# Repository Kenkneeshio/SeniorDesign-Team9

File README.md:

# SeniorDesign-Team9

Currently the GitHub Repo ignores .zip and .raw to save space

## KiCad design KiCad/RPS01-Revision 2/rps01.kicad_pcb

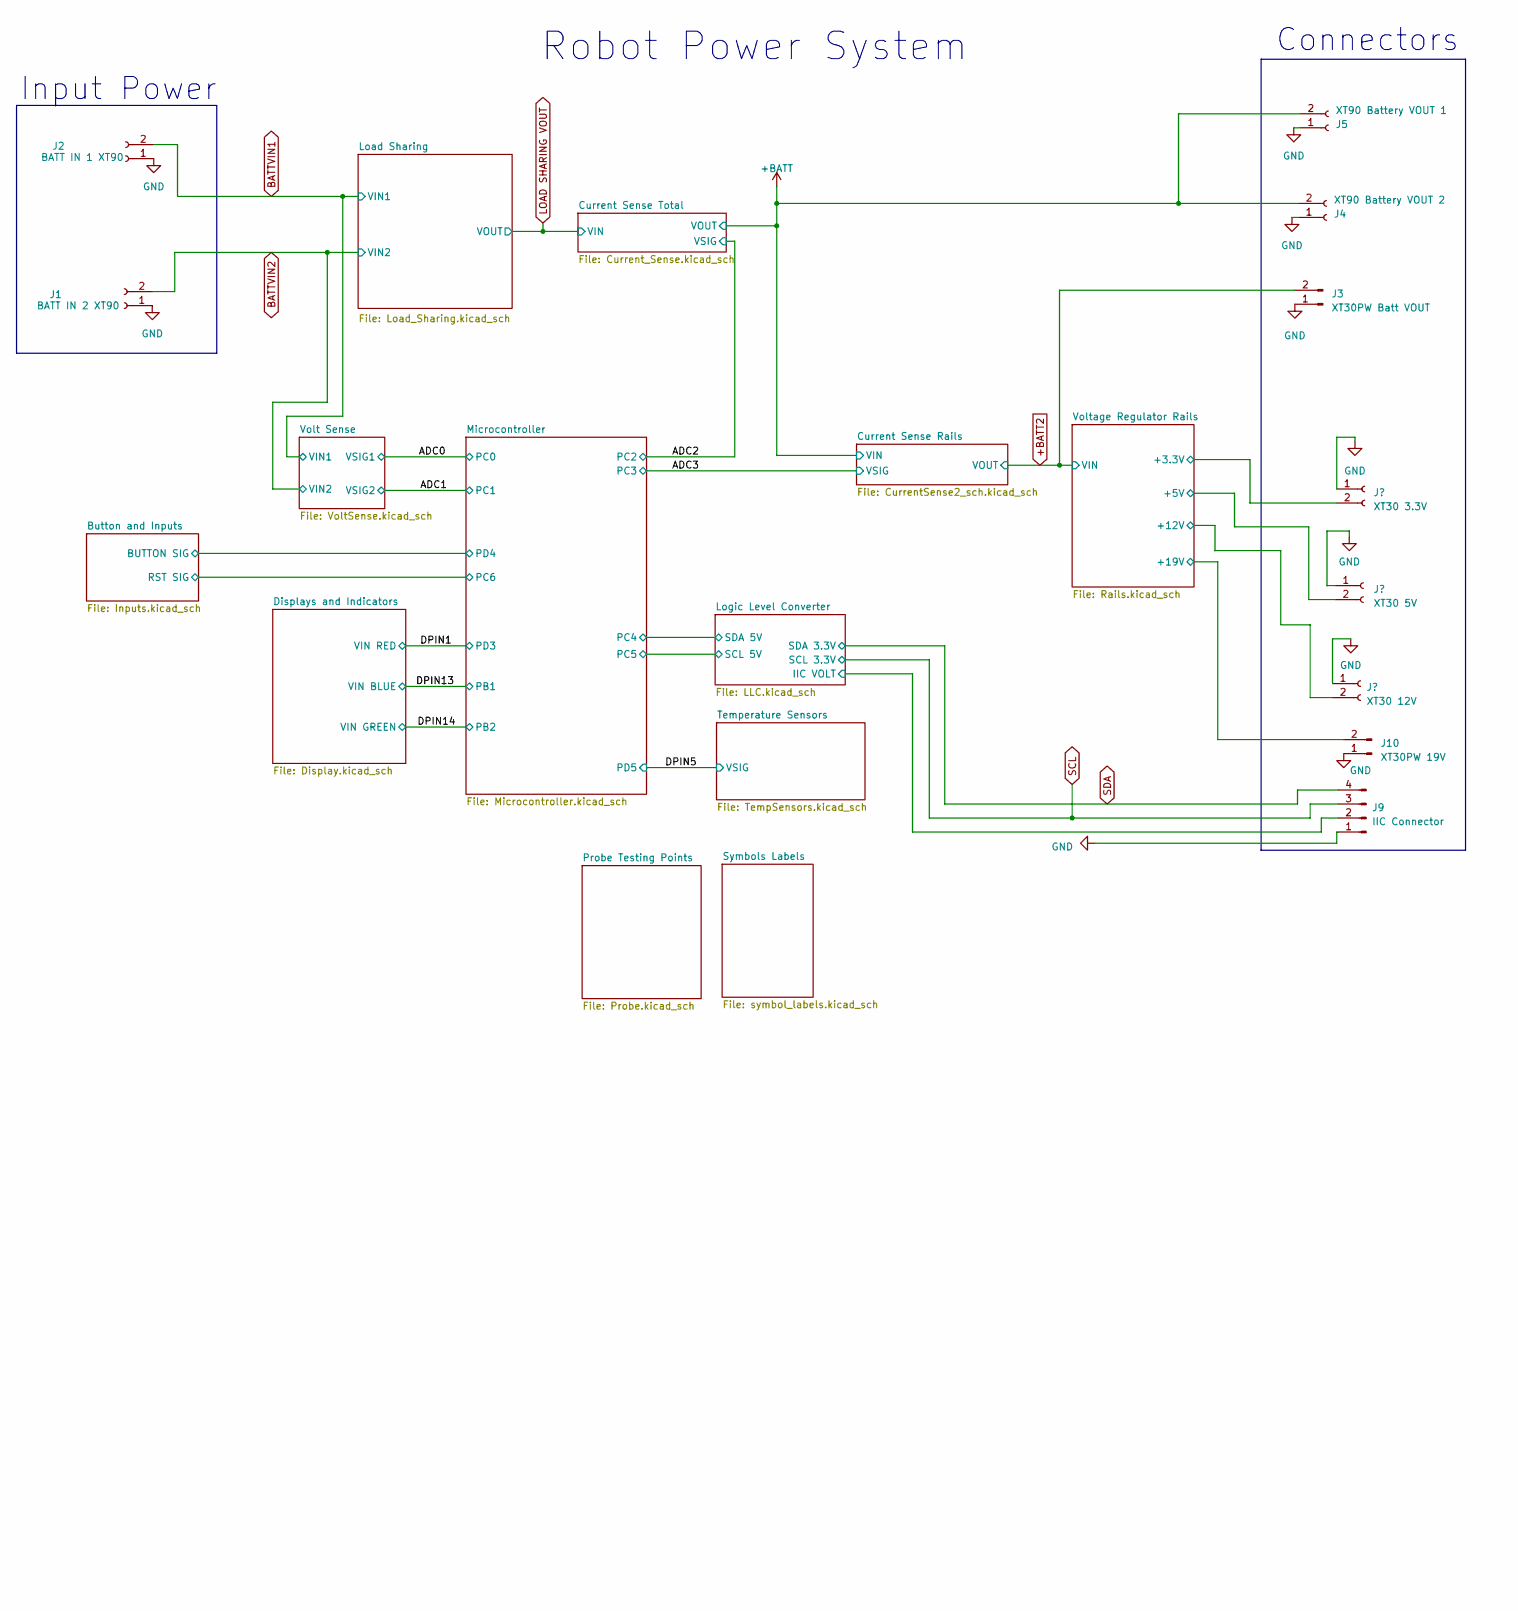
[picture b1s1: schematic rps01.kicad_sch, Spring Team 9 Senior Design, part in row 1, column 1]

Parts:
J1: BATT IN 2 XT90; AMASS_XT90-M_1x02_P11.00mm_Vertical
J2: BATT IN 1 XT90; AMASS_XT90-M_1x02_P11.00mm_Vertical
J3: XT30PW Batt VOUT; AMASS_XT30PW-F_1x02_P2.50mm_Horizontal
J4: XT90 Battery VOUT 2; AMASS_XT90-F_1x02_P11.00mm_Vertical
J5: XT90 Battery VOUT 1; AMASS_XT90-F_1x02_P11.00mm_Vertical
J6: XT30 12V; AMASS_XT30U-F_1x02_P5.0mm_Vertical
J7: XT30 5V; AMASS_XT30U-F_1x02_P5.0mm_Vertical
J8: XT30 3.3V; AMASS_XT30U-F_1x02_P5.0mm_Vertical
J9: IIC Connector; JST_PH_B4B-PH-K_1x04_P2.00mm_Vertical
J10: XT30PW 19V; AMASS_XT30PW-F_1x02_P2.50mm_Horizontal

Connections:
+3.3V: J8.2; also elsewhere on the board
+5V: J7.2; also elsewhere on the board
+12V: J6.2; also elsewhere on the board
+19V: J10.2; also elsewhere on the board
+BATT: J4.2, J5.2; also elsewhere on the board
+BATT2: J3.2; also elsewhere on the board
/Logic Level Converter/IIC VOLT: J9.2; also elsewhere on the board
SCL: J9.3; also elsewhere on the board
SDA: J9.4; also elsewhere on the board

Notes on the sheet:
Connectors
Robot Power System
Input Power

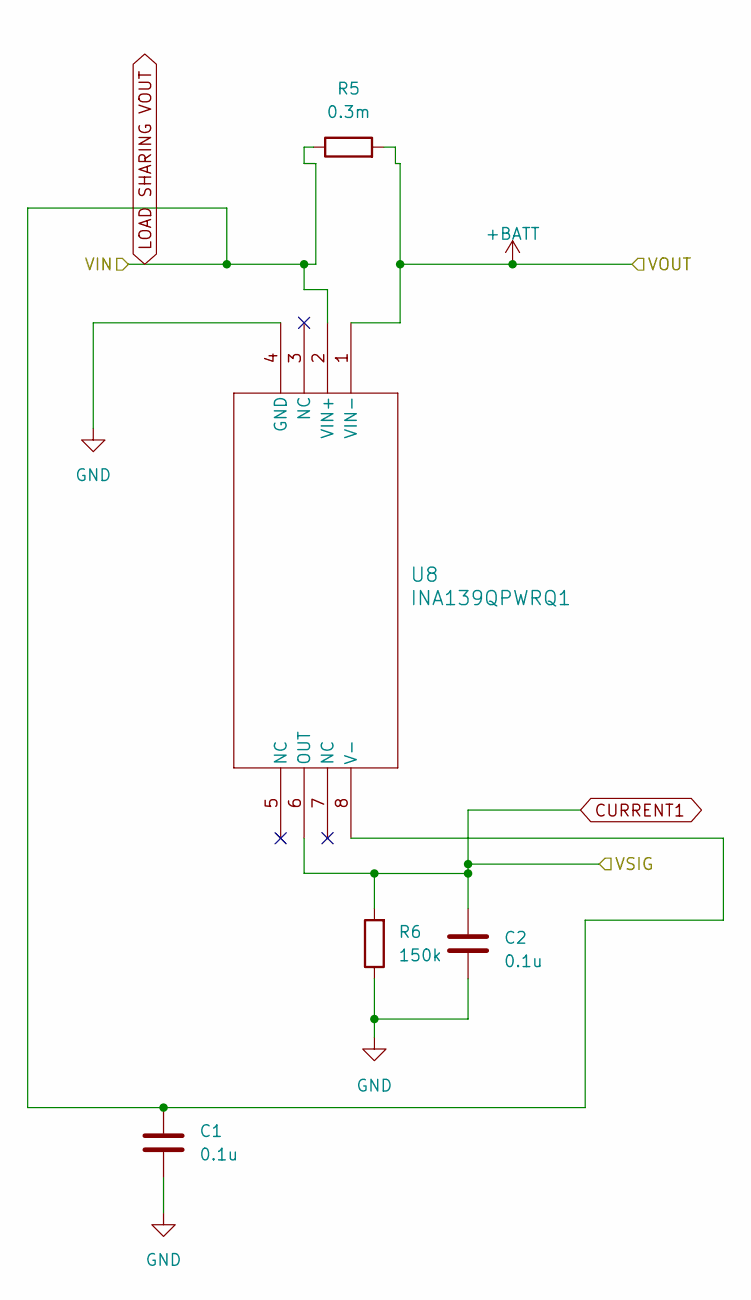
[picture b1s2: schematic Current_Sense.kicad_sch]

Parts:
C1, C2: 0.1u; C_0603_1608Metric
R5: 0.3m; CSS2H-5930R
R6: 150k; R_0603_1608Metric
U8: INA139QPWRQ1; INA139_PW8

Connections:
+BATT: R5.2, U8.1 (VIN-); also elsewhere on the board
CURRENT1: C2.1, R6.2, U8.6 (OUT); also elsewhere on the board
LOAD SHARING VOUT: C1.1, R5.1, U8.2 (VIN+), U8.8 (V-); also elsewhere on the board

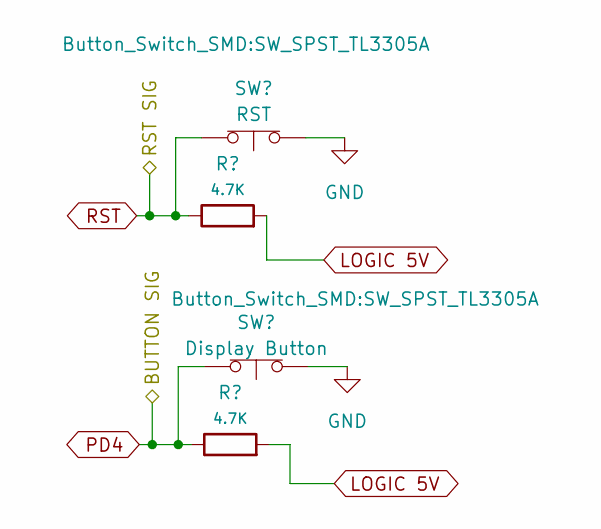
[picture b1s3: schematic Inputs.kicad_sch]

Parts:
R54, R55: 4.7K; R_0603_1608Metric
SW1: RST; SW_SPST_TL3305A
SW2: Display Button; SW_SPST_TL3305A

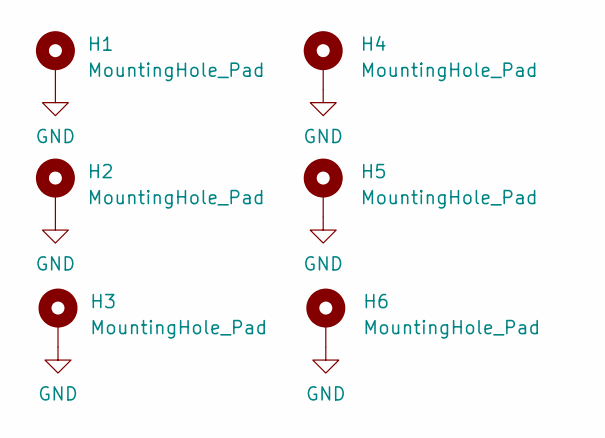
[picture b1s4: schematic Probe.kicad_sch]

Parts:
H1, H2, H3, H4, H5, H6: MountingHole_Pad; MountingHole_3.2mm_M3_Pad_Via

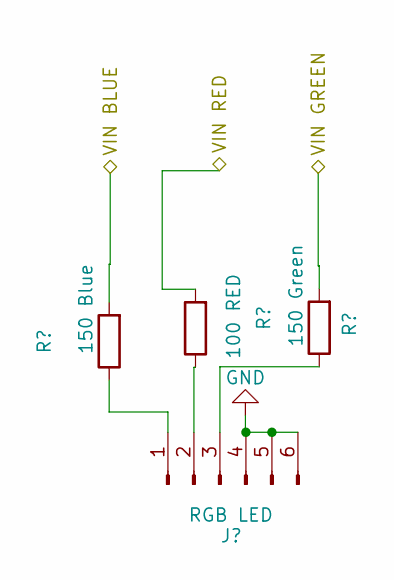
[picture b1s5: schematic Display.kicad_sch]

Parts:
J18: RGB LED; LED_RGB_5050-6
RBLUE1: 150 Blue; R_0603_1608Metric
RGREEN1: 150 Green; R_0603_1608Metric
RRED1: 100 RED; R_0603_1608Metric

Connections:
/DPIN1: RRED1.2; also elsewhere on the board
/DPIN14: RGREEN1.2; also elsewhere on the board
unnamed: J18.1, RBLUE1.1
unnamed: J18.2, RRED1.1
unnamed: J18.3, RGREEN1.1

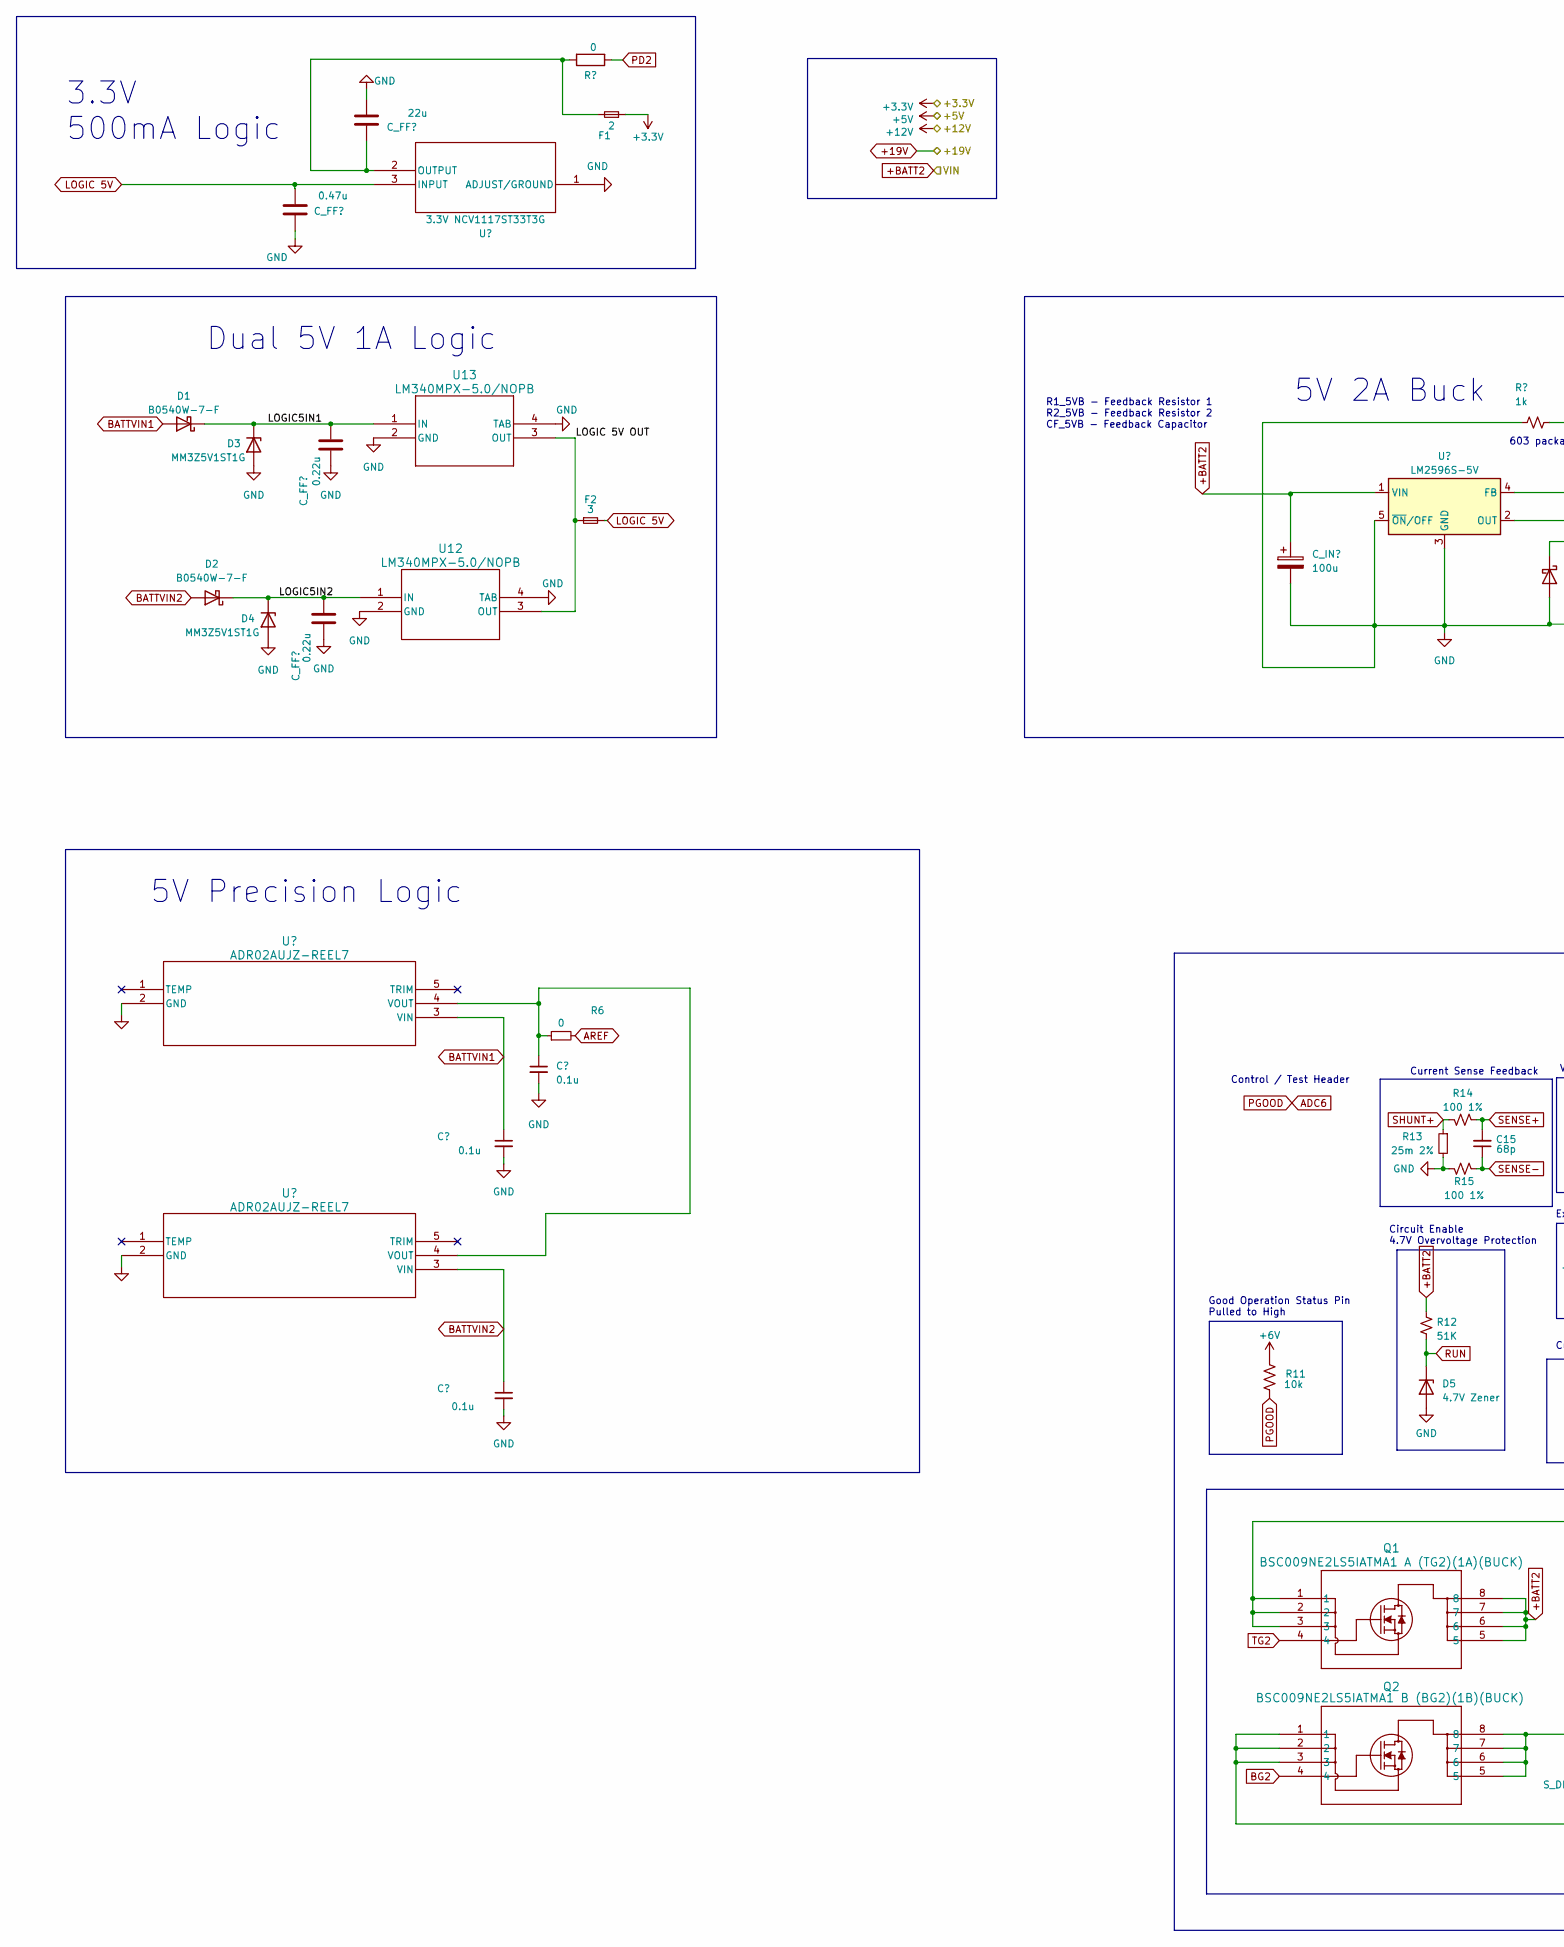
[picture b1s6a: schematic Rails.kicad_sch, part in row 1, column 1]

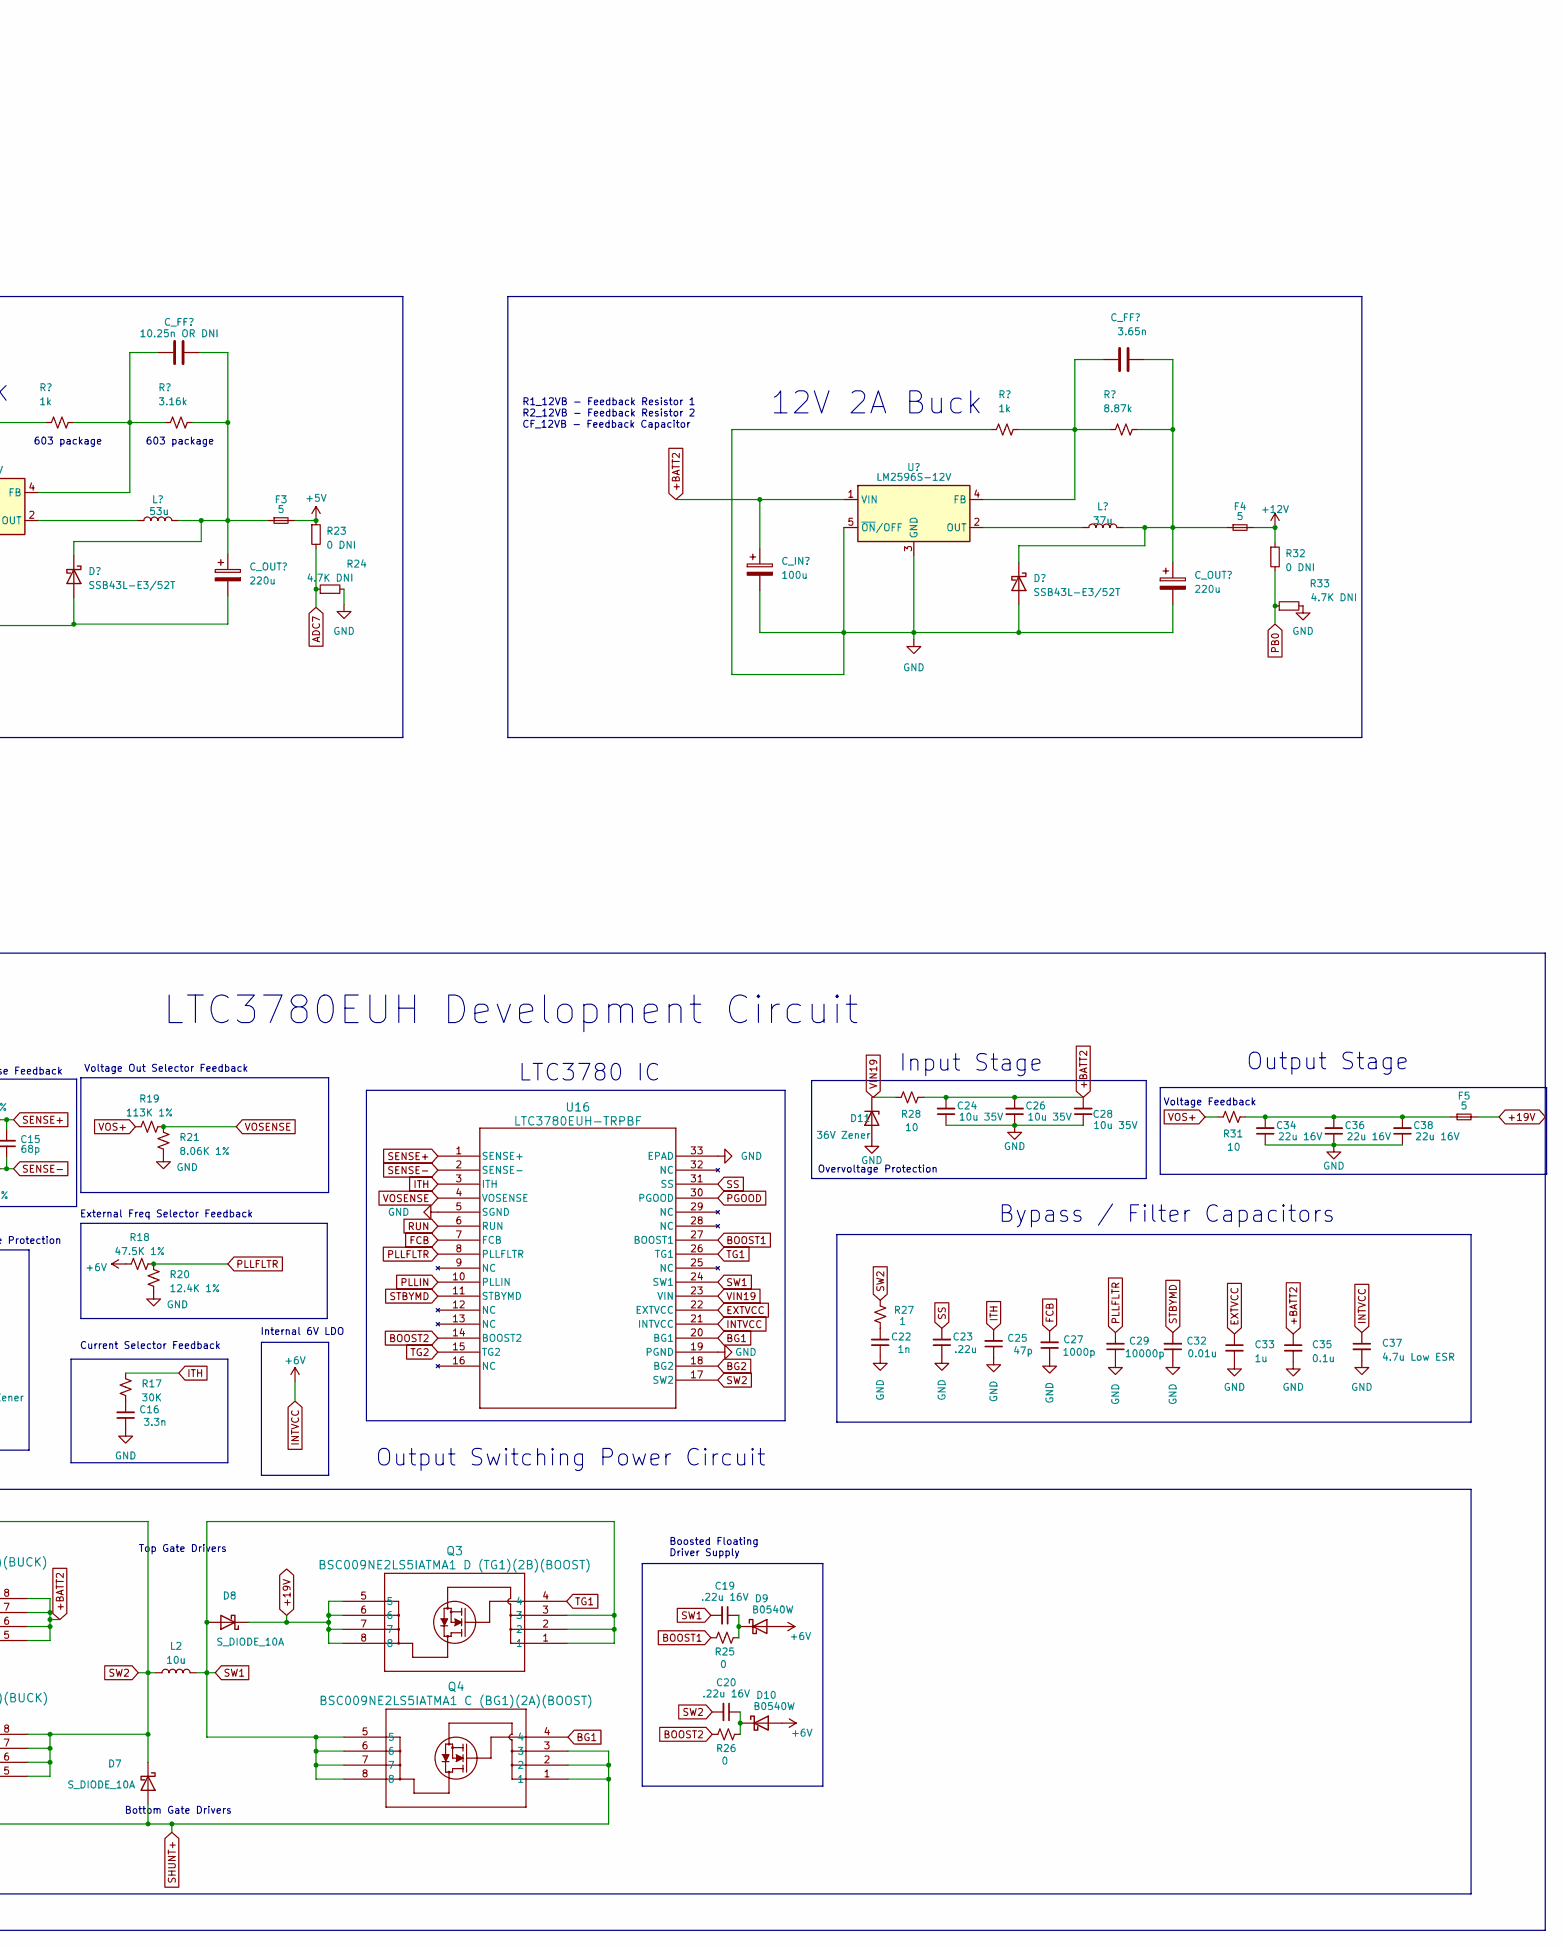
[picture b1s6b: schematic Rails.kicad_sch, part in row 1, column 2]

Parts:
C6, C7: 0.1u; C_0603_1608Metric
C8, C9: 0.22u; C_0603_1608Metric
C10: 22u; C_0603_1608Metric
C14, C21: 100u; CP_Elec_8x10
C15: 68p; C_1206_3216Metric_Pad1.33x1.80mm_HandSolder
C16: 3.3n; C_1206_3216Metric_Pad1.33x1.80mm_HandSolder
C17: 10.25n OR DNI; C_0603_1608Metric
C18, C31: 220u; CP_Elec_8x10
C19, C20: .22u 16V; C_1206_3216Metric_Pad1.33x1.80mm_HandSolder
C22: 1n; C_1206_3216Metric_Pad1.33x1.80mm_HandSolder
C23: .22u; C_1206_3216Metric_Pad1.33x1.80mm_HandSolder
C24, C26, C28: 10u 35V; C_1206_3216Metric_Pad1.33x1.80mm_HandSolder
C25: 47p; C_1206_3216Metric_Pad1.33x1.80mm_HandSolder
C27: 1000p; C_1206_3216Metric_Pad1.33x1.80mm_HandSolder
C29: 10000p; C_1206_3216Metric_Pad1.33x1.80mm_HandSolder
C30: 3.65n; C_0603_1608Metric
C32: 0.01u; C_1206_3216Metric_Pad1.33x1.80mm_HandSolder
C33: 1u; C_1206_3216Metric_Pad1.33x1.80mm_HandSolder
C34, C36, C38: 22u 16V; C_1206_3216Metric_Pad1.33x1.80mm_HandSolder
C35: 0.1u; C_1206_3216Metric_Pad1.33x1.80mm_HandSolder
C37: 4.7u Low ESR; LOWESRCAPMP7.6X4.3_3.1N_KEM
D1, D2: B0540W-7-F; D_SOD-123
D3, D4: MM3Z5V1ST1G; D_SOD-323
D5: 4.7V Zener; D_SOD-123
D6, D12: SSB43L-E3/52T; SSB43L-E352T_DIODE_DO214AA_MBRS
D7, D8: S_DIODE_10A; D_PowerDI-5
D9, D10: B0540W; CR_SMA_320-340AE_DIO
D11: 36V Zener; D_SOD-123
F1: 2; 0154Series_LTF
F2: 3; 0154Series_LTF
F3, F4, F5: 5; 0154Series_LTF
L1: 53u; PE-54039SNL_IND_HCI-68_PUL
L2: 10u; IND_410680_WRE
L3: 37u; PE-53932SNLT_IND_HCI-44_PUL
Q1: BSC009NE2LS5IATMA1 A (TG2)(1A)(BUCK); PG-TDSON-8_INF
Q2: BSC009NE2LS5IATMA1 B (BG2)(1B)(BUCK); PG-TDSON-8_INF
Q3: BSC009NE2LS5IATMA1 D (TG1)(2B)(BOOST); PG-TDSON-8_INF
Q4: BSC009NE2LS5IATMA1 C (BG1)(2A)(BOOST); PG-TDSON-8_INF
R6: 0; R_0603_1608Metric
R11: 10k; R_1206_3216Metric_Pad1.30x1.75mm_HandSolder
R12: 51K; R_1206_3216Metric_Pad1.30x1.75mm_HandSolder
R13: 25m 2%; R_2512_6332Metric_Pad1.40x3.35mm_HandSolder
R14, R15: 100 1%; R_1206_3216Metric_Pad1.30x1.75mm_HandSolder
R16, R29: 1k; R_0603_1608Metric
R17: 30K; R_1206_3216Metric_Pad1.30x1.75mm_HandSolder
R18: 47.5K 1%; R_1206_3216Metric_Pad1.30x1.75mm_HandSolder
R19: 113K 1%; R_1206_3216Metric_Pad1.30x1.75mm_HandSolder
R20: 12.4K 1%; R_1206_3216Metric_Pad1.30x1.75mm_HandSolder
R21: 8.06K 1%; R_1206_3216Metric_Pad1.30x1.75mm_HandSolder
R22: 3.16k; R_0603_1608Metric
R23, R32: 0 DNI; R_0603_1608Metric
R24, R33: 4.7K DNI; R_0603_1608Metric
R25, R26: 0; R_1206_3216Metric_Pad1.30x1.75mm_HandSolder
R27: 1; R_1206_3216Metric_Pad1.30x1.75mm_HandSolder
R28, R31: 10; R_1206_3216Metric_Pad1.30x1.75mm_HandSolder
R30: 8.87k; R_0603_1608Metric
RBLUE1: 0; R_0603_1608Metric
U9: ADR02AUJZ-REEL7; ADR02AUJZ_REEL7_UJ_5_ADI
U12, U13: LM340MPX-5.0/NOPB; SOT-223-3_TabPin2
U14: 3.3V NCV1117ST33T3G; SOT-223-3_TabPin2
U15: LM2596S-5V; TO-263-5_TabPin3
U16: LTC3780EUH-TRPBF; QFN-32_UH_LIT
U17: LM2596S-12V; TO-263-5_TabPin3

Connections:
+3.3V: F1.1; also elsewhere on the board
+5V: F3.2, R23.1; also elsewhere on the board
+12V: F4.2, R32.1; also elsewhere on the board
+19V: D8.1 (K), F5.2, Q3.5, Q3.6, Q3.7, Q3.8; also elsewhere on the board
+BATT2: C14.1, C21.1, C24.2, C26.2, C28.2, C35.1, Q1.5, Q1.6, Q1.7, Q1.8, R12.1, R28.1, U15.1 (VIN), U17.1 (VIN); also elsewhere on the board
/DPIN1: U9.1 (PD3); also elsewhere on the board
/Voltage Regulator Rails/LOGIC5IN1: C9.2, D1.1 (K), D3.1 (K), U13.1 (IN)
/Voltage Regulator Rails/LOGIC5IN2: C8.2, D2.1 (K), D4.1 (K), U12.1 (IN)
/Voltage Regulator Rails/LOGIC 5V OUT: F2.1, U12.3 (OUT), U13.3 (OUT)
ADC6: R11.2, U16.30 (PGOOD); also elsewhere on the board
ADC7: R23.2, R24.1; also elsewhere on the board
BG1: Q4.4, U16.20 (BG1)
BG2: Q2.4, U16.18 (BG2)
BOOST1: R25.1, U16.27 (BOOST1)
BOOST2: R26.1, U16.14 (BOOST2)
CURRENT1: R6.2; also elsewhere on the board
EXTVCC: C33.1, U16.22 (EXTVCC)
FCB: C27.2, U16.7 (FCB)
INTVCC: C37.1, D9.2 (A), D10.2 (A), R11.1, R18.1, U16.21 (INTVCC)
ITH: C25.2, R17.1, U16.3 (ITH)
unnamed: C16.2, R17.2
unnamed: C22.2, R27.1
unnamed: C34.2, C36.2, C38.2, F5.1, R31.1
unnamed: C17.2, C18.1, D6.1 (K), F3.1, L1.2, R22.2
unnamed: C19.1, D9.1 (K), R25.2
unnamed: C20.1, D10.1 (K), R26.2
unnamed: C30.2, C31.1, D12.1 (K), F4.1, L3.2, R30.2
unnamed 47: RBLUE1.1; also elsewhere on the board
unnamed: C17.1, R16.2, R22.1, U15.4 (FB)
unnamed: L1.1, U15.2 (OUT)
unnamed: C30.1, R29.2, R30.1, U17.4 (FB)
unnamed: L3.1, U17.2 (OUT)
PB0: R32.2, R33.1; also elsewhere on the board
PLLFLTR: C29.2, R18.2, R20.1, U16.8 (PLLFLTR)
PLLIN: U16.10 (PLLIN)
RUN: D5.1 (K), R12.2, U16.6 (RUN)
SENSE+: C15.2, R14.1, U16.1 (SENSE+)
SENSE-: C15.1, R15.1, U16.2 (SENSE-)
SHUNT+: D7.2 (A), Q2.1, Q2.2, Q2.3, Q4.1, Q4.2, Q4.3, R13.1, R14.2
SS: C23.2, U16.31 (SS)
STBYMD: C32.2, U16.11 (STBYMD)
SW1: C19.2, D8.2 (A), L2.2, Q3.1, Q3.2, Q3.3, Q4.5, Q4.6, Q4.7, Q4.8, U16.24 (SW1)
SW2: C20.2, D7.1 (K), L2.1, Q1.1, Q1.2, Q1.3, Q2.5, Q2.6, Q2.7, Q2.8, R27.2, U16.17 (SW2)
TG1: Q3.4, U16.26 (TG1)
TG2: Q1.4, U16.15 (TG2)
VIN19: D11.1 (K), R28.2, U16.23 (VIN)
VOS+: R19.1, R31.2
VOSENSE: R19.2, R21.1, U16.4 (VOSENSE)

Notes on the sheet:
Voltage Feedback
Overvoltage Protection
Top Gate Drivers
Voltage Out Selector Feedback
603 package
Good Operation Status Pin Pulled to High
R1_12VB - Feedback Resistor 1 R2_12VB - Feedback Resistor 2 CF_12VB - Feedback Capacitor
5V 2A Buck
5V Precision Logic
Current Selector Feedback
LTC3780EUH Development Circuit
External Freq Selector Feedback
Control / Test Header
LTC3780 IC
Input Stage
Dual 5V 1A Logic
Bottom Gate Drivers
Boosted Floating Driver Supply
Output Switching Power Circuit
Circuit Enable 4.7V Overvoltage Protection
R1_5VB - Feedback Resistor 1 R2_5VB - Feedback Resistor 2 CF_5VB - Feedback Capacitor
Current Sense Feedback
Output Stage
Bypass / Filter Capacitors
3.3V 500mA Logic
12V 2A Buck
Internal 6V LDO

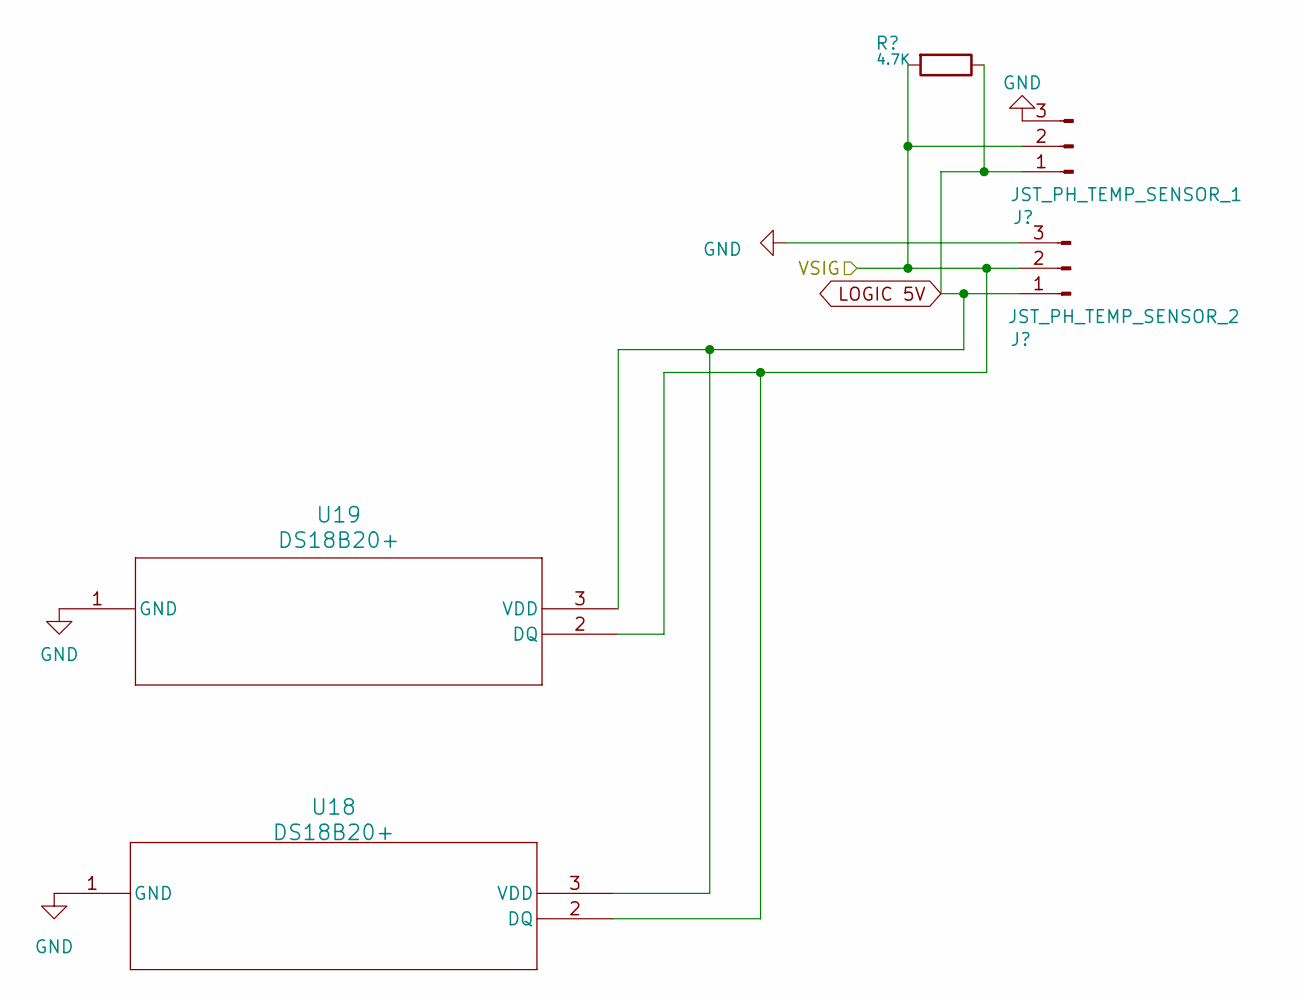
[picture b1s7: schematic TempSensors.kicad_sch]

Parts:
J16: JST_PH_TEMP_SENSOR_2; JST_PH_B3B-PH-K_1x03_P2.00mm_Vertical
J17: JST_PH_TEMP_SENSOR_1; JST_PH_B3B-PH-K_1x03_P2.00mm_Vertical
R44: 4.7K; R_0603_1608Metric
U18, U19: DS18B20+; TO-92L_Inline

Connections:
/DPIN5: J16.2, J17.2, R44.2, U18.2 (DQ), U19.2 (DQ); also elsewhere on the board

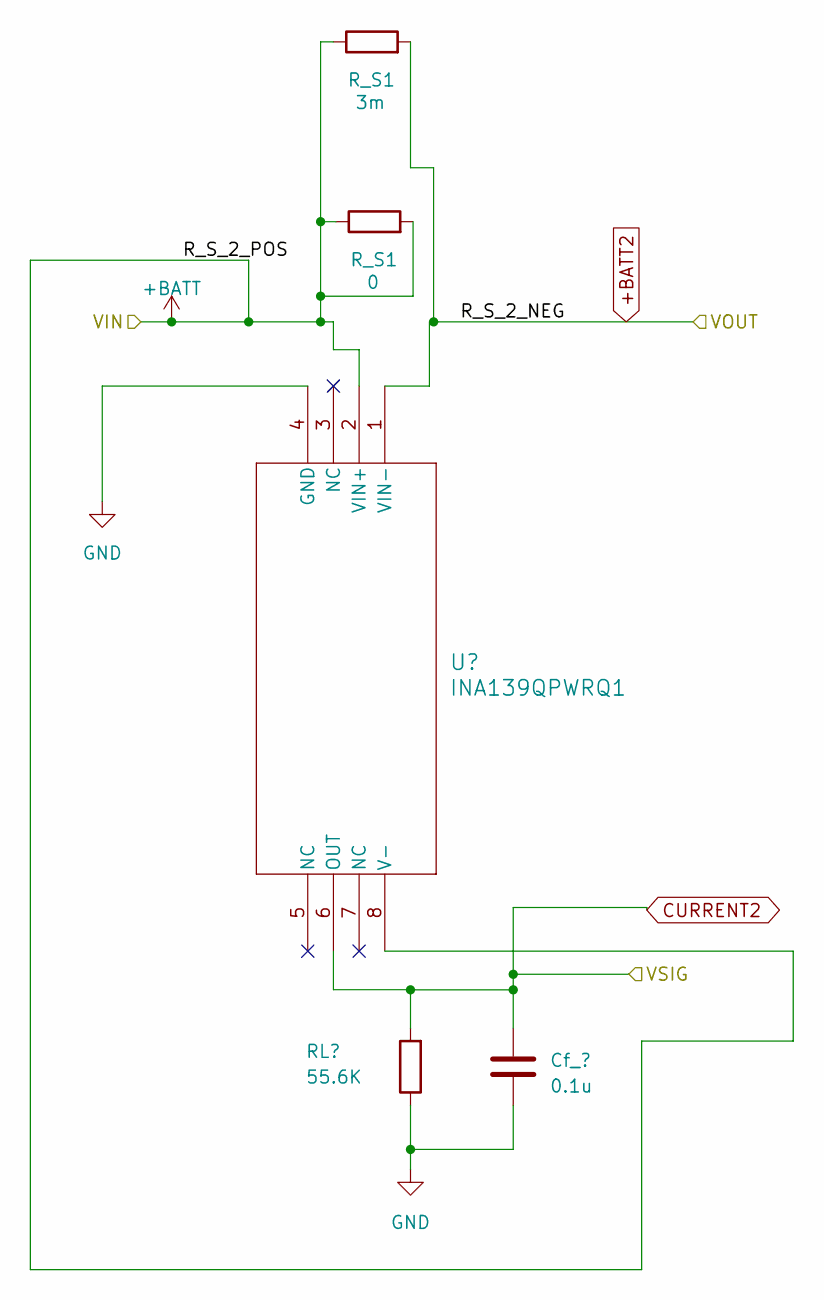
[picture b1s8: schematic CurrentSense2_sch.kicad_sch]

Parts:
C41: 0.1u; C_0603_1608Metric
R53: 55.6K; R_0603_1608Metric
R_S1: 0; CSS2H-5930R
U22: INA139QPWRQ1; INA139_PW8

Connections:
+BATT: U22.2 (VIN+), U22.8 (V-); also elsewhere on the board
+BATT2: U22.1 (VIN-); also elsewhere on the board
CURRENT2: C41.1, R53.2, U22.6 (OUT); also elsewhere on the board

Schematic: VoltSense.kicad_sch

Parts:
C39, C40: 0.1u; C_0603_1608Metric
D13, D14: MMSZ5247BT1G; D_SOD-123
R45, R46: 1.2M; R_1206_3216Metric
R47, R48: 510K; R_1206_3216Metric
R49, R50: 0; R_0603_1608Metric_Pad0.98x0.95mm_HandSolder
U20, U21: UA741CDT; UA741CDT_D8_TEX_STM

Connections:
unnamed: R46.2, R48.1, R49.1, U20.3 (NON-INVERTING_INPUT)
unnamed: R45.2, R47.1, R50.1, U21.3 (NON-INVERTING_INPUT)
VOLT1: C40.1, D14.1 (K), R50.2, U21.2 (INVERTING_INPUT), U21.6 (OUTPUT); also elsewhere on the board
VOLT2: C39.1, D13.1 (K), R49.2, U20.2 (INVERTING_INPUT), U20.6 (OUTPUT); also elsewhere on the board

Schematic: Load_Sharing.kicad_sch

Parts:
R1, R2: 0; R_0603_1608Metric
R3, R4: 99999; R_0603_1608Metric
U1: LTC4416EMS-1-TRPBF; LTC4416_MSOP-10_MS_LIT
U2, U3, U4, U5, U6, U7: NP100P04PLG-E1-AY; LTC3780_PRSS0004AL-A_REN

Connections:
/Load Sharing/E1: R1.2, R3.2, U1.2 (E1)
/Load Sharing/E2: R2.1, R4.1, U1.4 (*E2)
/Load Sharing/G1: U1.10 (G1), U2.1 (GATE), U3.1 (GATE), U4.1 (GATE)
/Load Sharing/G2: U1.6 (G2), U5.1 (GATE), U6.1 (GATE), U7.1 (GATE)
LOAD SHARING VOUT: U1.8 (VS), U2.3 (SOURCE), U3.3 (SOURCE), U4.3 (SOURCE), U5.3 (SOURCE), U6.3 (SOURCE), U7.3 (SOURCE); also elsewhere on the board
PD6: R3.1; also elsewhere on the board
PD7: R4.2; also elsewhere on the board

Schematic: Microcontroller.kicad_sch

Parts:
C3: 0.1u; C_0603_1608Metric
C4, C5: 22p; C_0603_1608Metric
C6: 100n; C_0603_1608Metric
J11: Serial; PinHeader_1x05_P2.54mm_Horizontal
J12: ISCP; PinHeader_2x03_P2.54mm_Vertical
R7, R8: 4.7k; R_0603_1608Metric
U9: ATmega328P-A; TQFP-32_7x7mm_P0.8mm
Y1: 16M; Crystal_SMD_HC49-SD

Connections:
/DPIN1: U9.1 (PD3); also elsewhere on the board
/DPIN5: U9.9 (PD5); also elsewhere on the board
/DPIN14: U9.14 (PB2); also elsewhere on the board
/Microcontroller/MISO: J12.1, U9.16 (PB4)
/Microcontroller/MOSI: J12.5, U9.15 (PB3)
/Microcontroller/PC4: U9.27 (PC4); also elsewhere on the board
/Microcontroller/PC5: U9.28 (PC5); also elsewhere on the board
/Microcontroller/RX: J11.3, U9.30 (PD0)
/Microcontroller/SCK: J12.2, U9.17 (PB5)
/Microcontroller/TX: J11.4, U9.31 (PD1)
/Microcontroller/XTAL1: C4.1, U9.7 (XTAL1/PB6), Y1.1
/Microcontroller/XTAL2: C5.1, U9.8 (XTAL2/PB7), Y1.2
ADC6: U9.19 (ADC6); also elsewhere on the board
ADC7: U9.22 (ADC7); also elsewhere on the board
AREF: U9.20 (AREF); also elsewhere on the board
CURRENT1: U9.25 (PC2); also elsewhere on the board
CURRENT2: U9.26 (PC3); also elsewhere on the board
PB0: U9.12 (PB0); also elsewhere on the board
PD2: U9.32 (PD2); also elsewhere on the board
PD6: R7.1, U9.10 (PD6); also elsewhere on the board
PD7: R8.1, U9.11 (PD7); also elsewhere on the board
VOLT1: U9.23 (PC0); also elsewhere on the board
VOLT2: U9.24 (PC1); also elsewhere on the board

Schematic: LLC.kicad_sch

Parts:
Q5, Q6: BSS138; SOT-23
R34: 0 DNI; R_0603_1608Metric
R35, R38, R39: 0; R_0603_1608Metric
R36, R37, R40, R41: 10K; R_0603_1608Metric
R42, R43: 4.7K; R_0603_1608Metric

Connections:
+3.3V: Q5.1 (G), Q6.1 (G), R34.2, R36.1, R37.1; also elsewhere on the board
+5V: R35.1; also elsewhere on the board
/Logic Level Converter/IIC VOLT: R34.1, R35.2; also elsewhere on the board
/Microcontroller/PC4: Q5.3 (D), R38.2, R40.2, R42.2; also elsewhere on the board
/Microcontroller/PC5: Q6.3 (D), R39.2, R41.2, R43.2; also elsewhere on the board
SCL: Q6.2 (S), R37.2, R39.1; also elsewhere on the board
SDA: Q5.2 (S), R36.2, R38.1; also elsewhere on the board

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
